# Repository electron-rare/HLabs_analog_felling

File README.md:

# HLabs_analog_felling

in progress : HLabs analog_felling for stereo preamp

PCB and CODE for constant output of a preamp with motorised potentiometer in I2C

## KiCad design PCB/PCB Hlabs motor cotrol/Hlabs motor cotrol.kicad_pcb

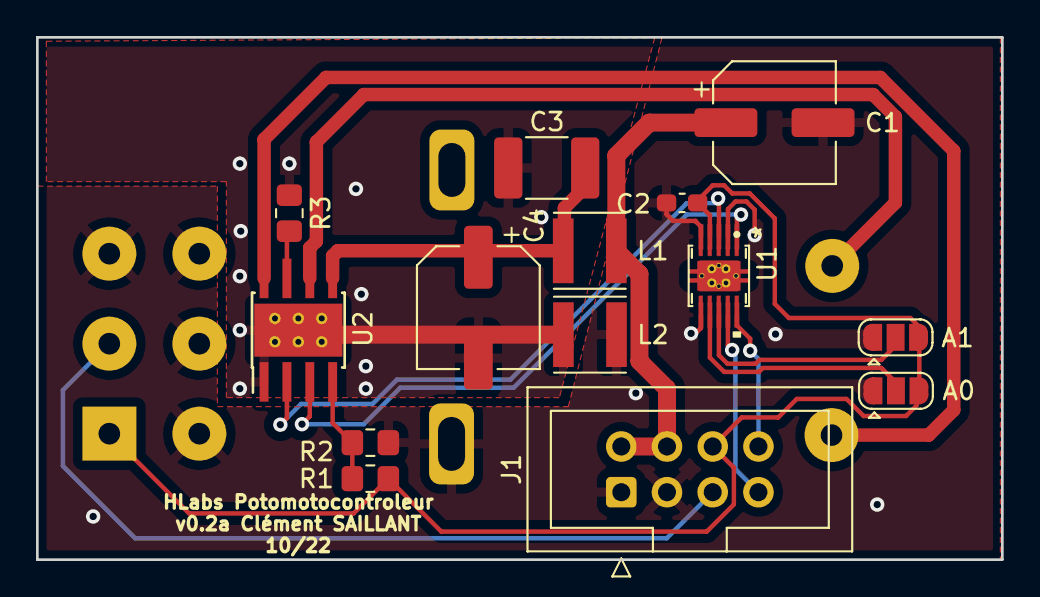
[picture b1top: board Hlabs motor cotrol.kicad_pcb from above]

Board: 2 copper layers, 53.6 x 29.0 mm, 15 parts (1 on the bottom side), 16 nets.

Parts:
A0, A1: SolderJumper_3_Open; SolderJumper-3_P1.3mm_Open_RoundedPad1.0x1.5mm
C1: 220uF; CP_Elec_6.3x7.7
C2: 100nF; C_0603_1608Metric_Pad1.08x0.95mm_HandSolder
C3: 0.1uF; C_1812_4532Metric_Pad1.57x3.40mm_HandSolder
C4: 47uF; CP_Elec_6.3x5.4
J1: Conn_02x04_Odd_Even; IDC-Header_2x04_P2.54mm_Vertical
L1: 220uH; L_Vishay_IFSC-1515AH_4x4x1.8mm
L2: 220mH; L_Vishay_IFSC-1515AH_4x4x1.8mm
R1: 5k; R_0805_2012Metric_Pad1.20x1.40mm_HandSolder
R2: 7,5k; R_0805_2012Metric_Pad1.20x1.40mm_HandSolder
R3: 1,5R 0,1% 0,5W; R_0805_2012Metric_Pad1.20x1.40mm_HandSolder
RV1: Motorized_Potentiometer; Potentiometer_RC-1601
U1: DRV8830DGQ
U2: DRV8870DDA; Texas_HTSOP-8-1EP_3.9x4.9mm_P1.27mm_EP2.95x4.9mm_Mask2.4x3.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

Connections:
+5V: A0.3 (B), A1.3 (B), C2.1, J1.6, R1.1, RV1.1, U1.4 (VCC)
+Vmot: C3.1, C4.1, L1.2, U2.5 (VM)
/M+: RV1.M+, U2.6 (OUT1)
/VMOT: C1.1, J1.2, J1.4, L1.1
A0: A0.2 (C), U1.7 (A0)
A1: A1.2 (C), U1.8 (A1)
GND: A0.1 (A), A1.1 (A), C1.2, C2.2, J1.1, J1.3, L2.1, R2.2, RV1.3, RV1.4, RV1.5, RV1.6, RV1.GND, U1.2 (ISENSE), U1.5 (GND), U1.6 (FAULTN), U1.EPAD, U1.V
GND1: C3.2, C4.2, L2.2, R3.2, U2.1 (GND), U2.9 (GND)
I2C SCL: J1.8, U1.10 (SCL)
I2C SDA: J1.7, U1.9 (SDA)
unnamed: R1.2, R2.1, U2.4 (VREF)
unnamed: R3.1, U2.7 (ISEN)
unnamed: RV1.M-, U2.8 (OUT2)
unnamed: U1.1 (OUT2), U2.3 (IN1)
unnamed: U1.3 (OUT1), U2.2 (IN2)
pot_cmd: J1.5, RV1.2

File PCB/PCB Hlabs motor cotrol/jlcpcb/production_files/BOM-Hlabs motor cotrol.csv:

Comment,Designator,Footprint,LCSC
100nF,C2,C_0603_1608Metric_Pad1.08x0.95mm_HandSolder,C66501
DRV8830DGQ,U1,DRV8830DGQ,
Conn_02x04_Odd_Even,J1,IDC-Header_2x04_P2.54mm_Vertical,
Motorized_Potentiometer,RV1,Potentiometer_RC-1601,
"1,5R 0,1% 0,5W",R3,R_0805_2012Metric_Pad1.20x1.40mm_HandSolder,
0.1uF,C3,C_1812_4532Metric_Pad1.57x3.40mm_HandSolder,
220uF,C1,CP_Elec_6.3x7.7,
"7,5k",R2,R_0805_2012Metric_Pad1.20x1.40mm_HandSolder,
5k,R1,R_0805_2012Metric_Pad1.20x1.40mm_HandSolder,
DRV8870DDA,U2,Texas_HTSOP-8-1EP_3.9x4.9mm_P1.27mm_EP2.95x4.9mm_Mask2.4x3.1mm_ThermalVias,
220uH,L1,L_Vishay_IFSC-1515AH_4x4x1.8mm,
SolderJumper_3_Open,A0,SolderJumper-3_P1.3mm_Open_RoundedPad1.0x1.5mm,
SolderJumper_3_Open,A1,SolderJumper-3_P1.3mm_Open_RoundedPad1.0x1.5mm,
47uF,C4,CP_Elec_6.3x5.4,
220mH,L2,L_Vishay_IFSC-1515AH_4x4x1.8mm,

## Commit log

2023-01-25 new file: .gitignore new file: .vscode/extensions.json new file: .vscode/settings.json new file: platformio.ini new file: src/.DS_Store new file: src/bouton.h new file: src/const_set.h new file: src/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
2023-01-25 modified: platformio.ini
2023-01-25 modified: .gitignore
2023-01-25 changement sens de commutation relais
2023-02-27 clean code
2023-02-27 platformIO clean
2023-03-09 with PID & control calc OK
2023-03-17 implémentation stereo_link
2023-03-17 stereo_link implémentation
2023-09-12 update to github
2023-09-15 update code
2023-09-15 update folder tree
2023-09-15 clean file
2023-09-21 update I2C adresse
2023-09-21 update bit resolution

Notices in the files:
parts and their libraries:
Copyright 2021 Accelerated Designs. All rights reserved.
